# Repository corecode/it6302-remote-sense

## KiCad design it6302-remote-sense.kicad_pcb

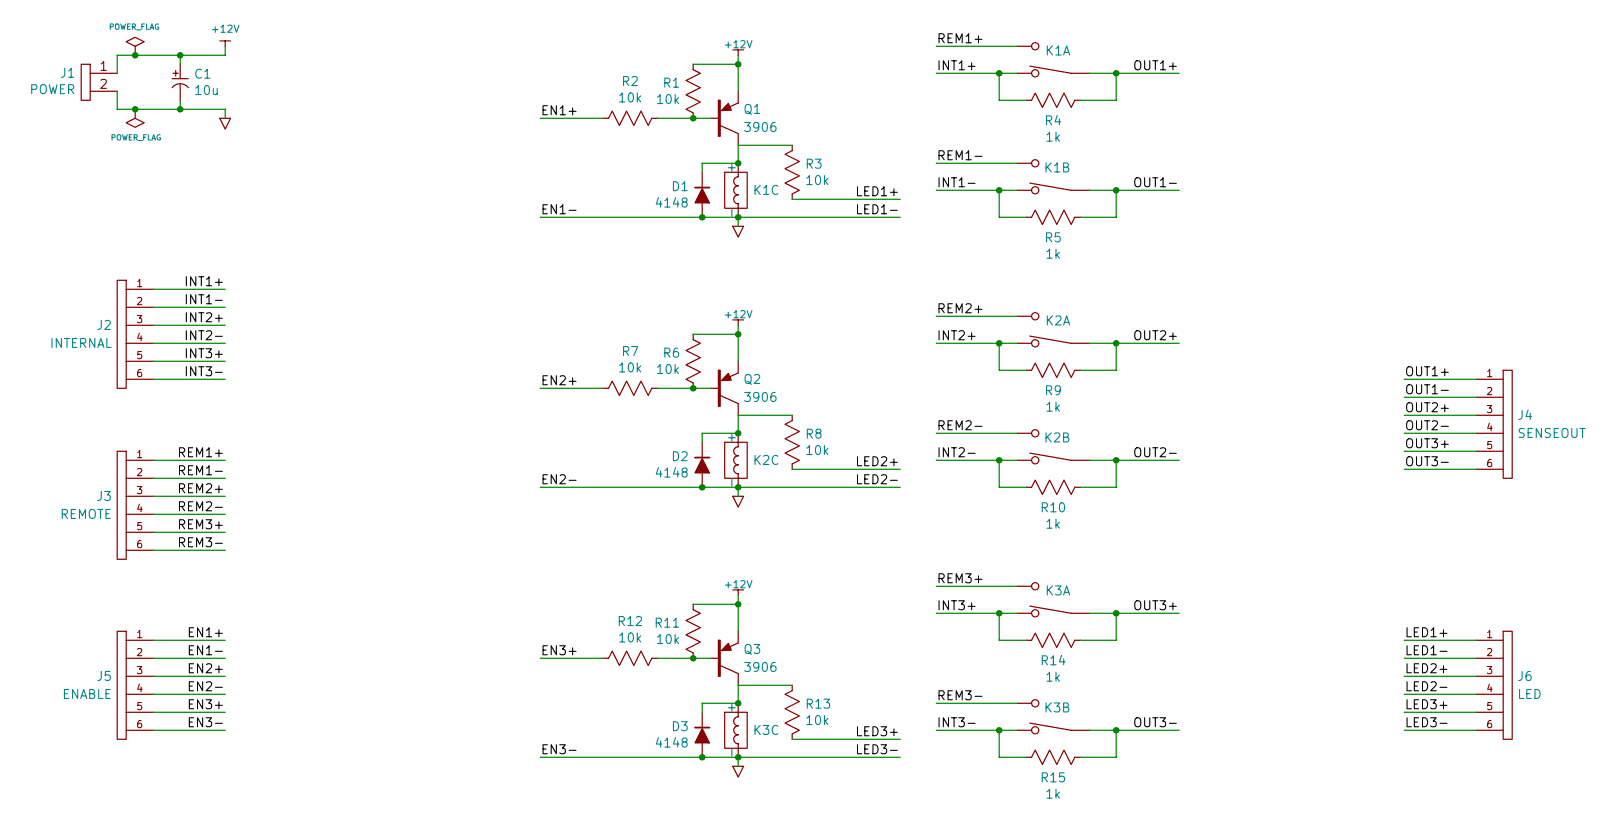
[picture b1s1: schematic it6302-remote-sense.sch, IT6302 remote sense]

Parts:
C1: 10u; SMD-CP-6.3
D1, D2, D3: 4148; SOT-23-DIODE
J1: POWER; JST-XH-2-PTH-TOP
J2: INTERNAL; JST-XH-6-PTH-TOP
J3: REMOTE; JST-XH-6-PTH-TOP
J4: SENSEOUT; JST-XH-6-PTH-TOP
J5: ENABLE; JST-XH-6-PTH-TOP
J6: LED; JST-XH-6-PTH-TOP
K1, K2, K3: RELAY-DPDT-EE2-SPLIT; RELAY-EE2-NU
Q1, Q2, Q3: 3906; SOT-23-BJT
R1, R2, R3, R6, R7, R8, R11, R12, R13: 10k; SMD-1608
R4, R5, R9, R10, R14, R15: 1k; SMD-1608

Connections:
/EN1+: J5.1, R2.1
/EN2+: J5.3, R7.1
/EN3+: J5.5, R12.1
/INT1+: J2.1, K1.3, R4.1
/INT1-: J2.2, K1.10, R5.1
/INT2+: J2.3, K2.3, R9.1
/INT2-: J2.4, K2.10, R10.1
/INT3+: J2.5, K3.3, R14.1
/INT3-: J2.6, K3.10, R15.1
/LED1+: J6.1, R3.2
/LED2+: J6.3, R8.2
/LED3+: J6.5, R13.2
/OUT1+: J4.1, K1.4, R4.2
/OUT1-: J4.2, K1.9, R5.2
/OUT2+: J4.3, K2.4, R9.2
/OUT2-: J4.4, K2.9, R10.2
/OUT3+: J4.5, K3.4, R14.2
/OUT3-: J4.6, K3.9, R15.2
/REM1+: J3.1, K1.5
/REM1-: J3.2, K1.8
/REM2+: J3.3, K2.5
/REM2-: J3.4, K2.8
/REM3+: J3.5, K3.5
/REM3-: J3.6, K3.8
unnamed: D1.C, K1.1 (+), Q1.C, R3.1
unnamed: D2.C, K2.1 (+), Q2.C, R8.1
unnamed: D3.C, K3.1 (+), Q3.C, R13.1
unnamed: Q1.B, R1.2, R2.2
unnamed: Q2.B, R6.2, R7.2
unnamed: Q3.B, R11.2, R12.2

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
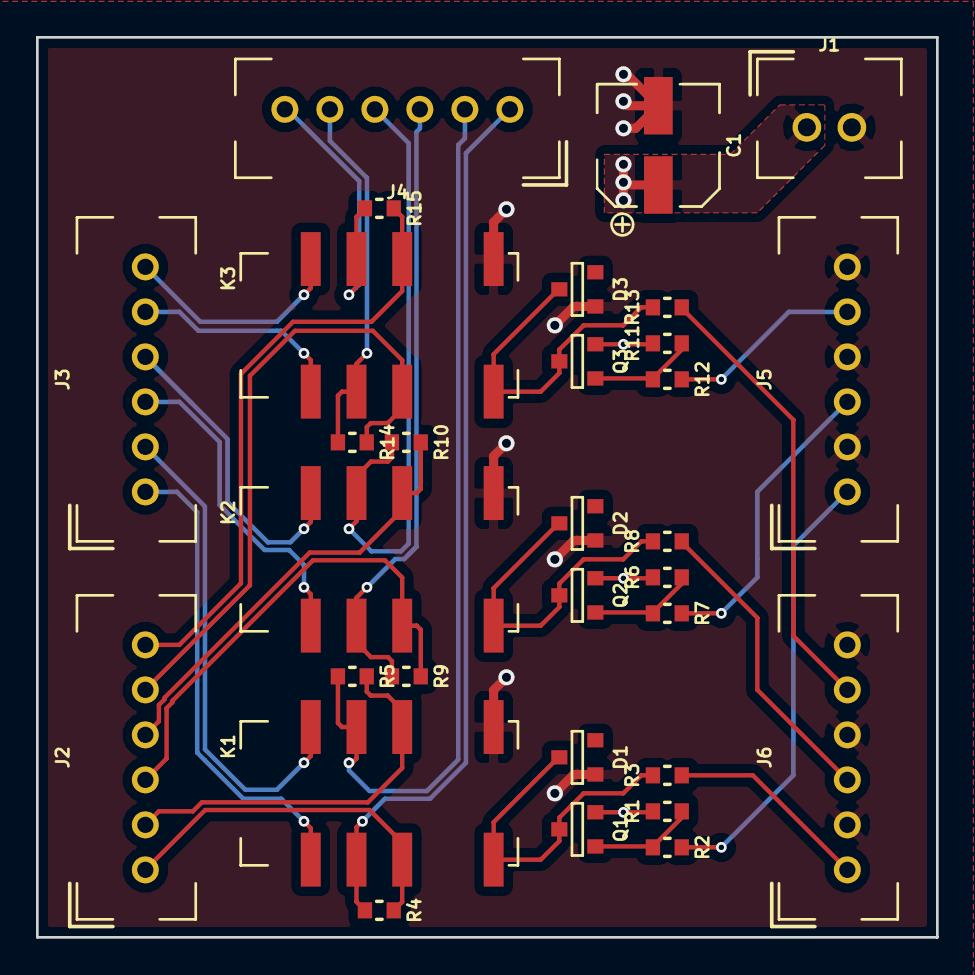
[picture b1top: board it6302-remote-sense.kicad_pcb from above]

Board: 2 copper layers, 50.0 x 50.0 mm, 31 parts (0 on the bottom side), 32 nets.

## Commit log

2017-01-24 start itech it6302 remote sense module
2017-02-03 start layout
